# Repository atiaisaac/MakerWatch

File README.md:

# MakerWatch

## About
An open source smartwatch built by a maker for the maker community packed with interesting features and runs on the zephry RTOS

## Hardware
Outlined below is a breakdown of the hardware componenets considered for this design;

* __NINA-B306__ module (nrf52840 based microcontroller)
    * 1MB flash memory
    * 256KB of RAM
    * Bluetooth LE
    * internal pcb antenna
* __LSM6DSOX__ IMU with 6-DOF from stmicroelectronics. Primarily for step counting (pedometer) and other cool navigation gestures.
* __NPM1300__ single cell li-ion charger with power path managament. It also includes 2 buck converters capable of providing 200mA each and 3 LDOs. More than enough for our setup. When paired with the right nrf chipset, it can serve as a fuel guage as well.
* __MAX86141__ an AFE for optical data acquisition. Paired with MAX32664
* __MAX32664__ an ultra-low power biometric sensor hub with embedded firmware for heart rate monitoring and blood oxygen saturation measurement.
* __KX122__ paired with MAX32664 to compensate for artifacts of motion required for proper HRM and SpO2 measurement.
* __FIREFLY E2218__ true green color for health monitoring i.e HRM and pulse oximetry
* __SFH 7015__ hyper-red and infrared for HRM and pulse oximetry.
* __SFH 2703__ is a photodiode for capturing reflected light needed by the HRM and SpO2 algorithm
* 1.28'' round tft display with __GC9a01__ display driver
* __RV-8263-C8__ crystal to serve as real time clock/calendar
* __USB-C__ interface for easy flashing of firmware for developers/makers

The hardware setup is made up of two board stacked together back to back my a mezzinine connector. There is the main watch board and what I have dubbed the ppg board that has the leds for photoplethysemography.

## Software
The MakerWatch uses a usb-c as the main source of flashing new firmware. However, on the board, there are breakout pads that serve as Serial Wire Debug (SWD) interface for doing other cool stuff like ITM when paired with the right hardware programmer. In this version, wires will have to be soldered onto the pads before use.

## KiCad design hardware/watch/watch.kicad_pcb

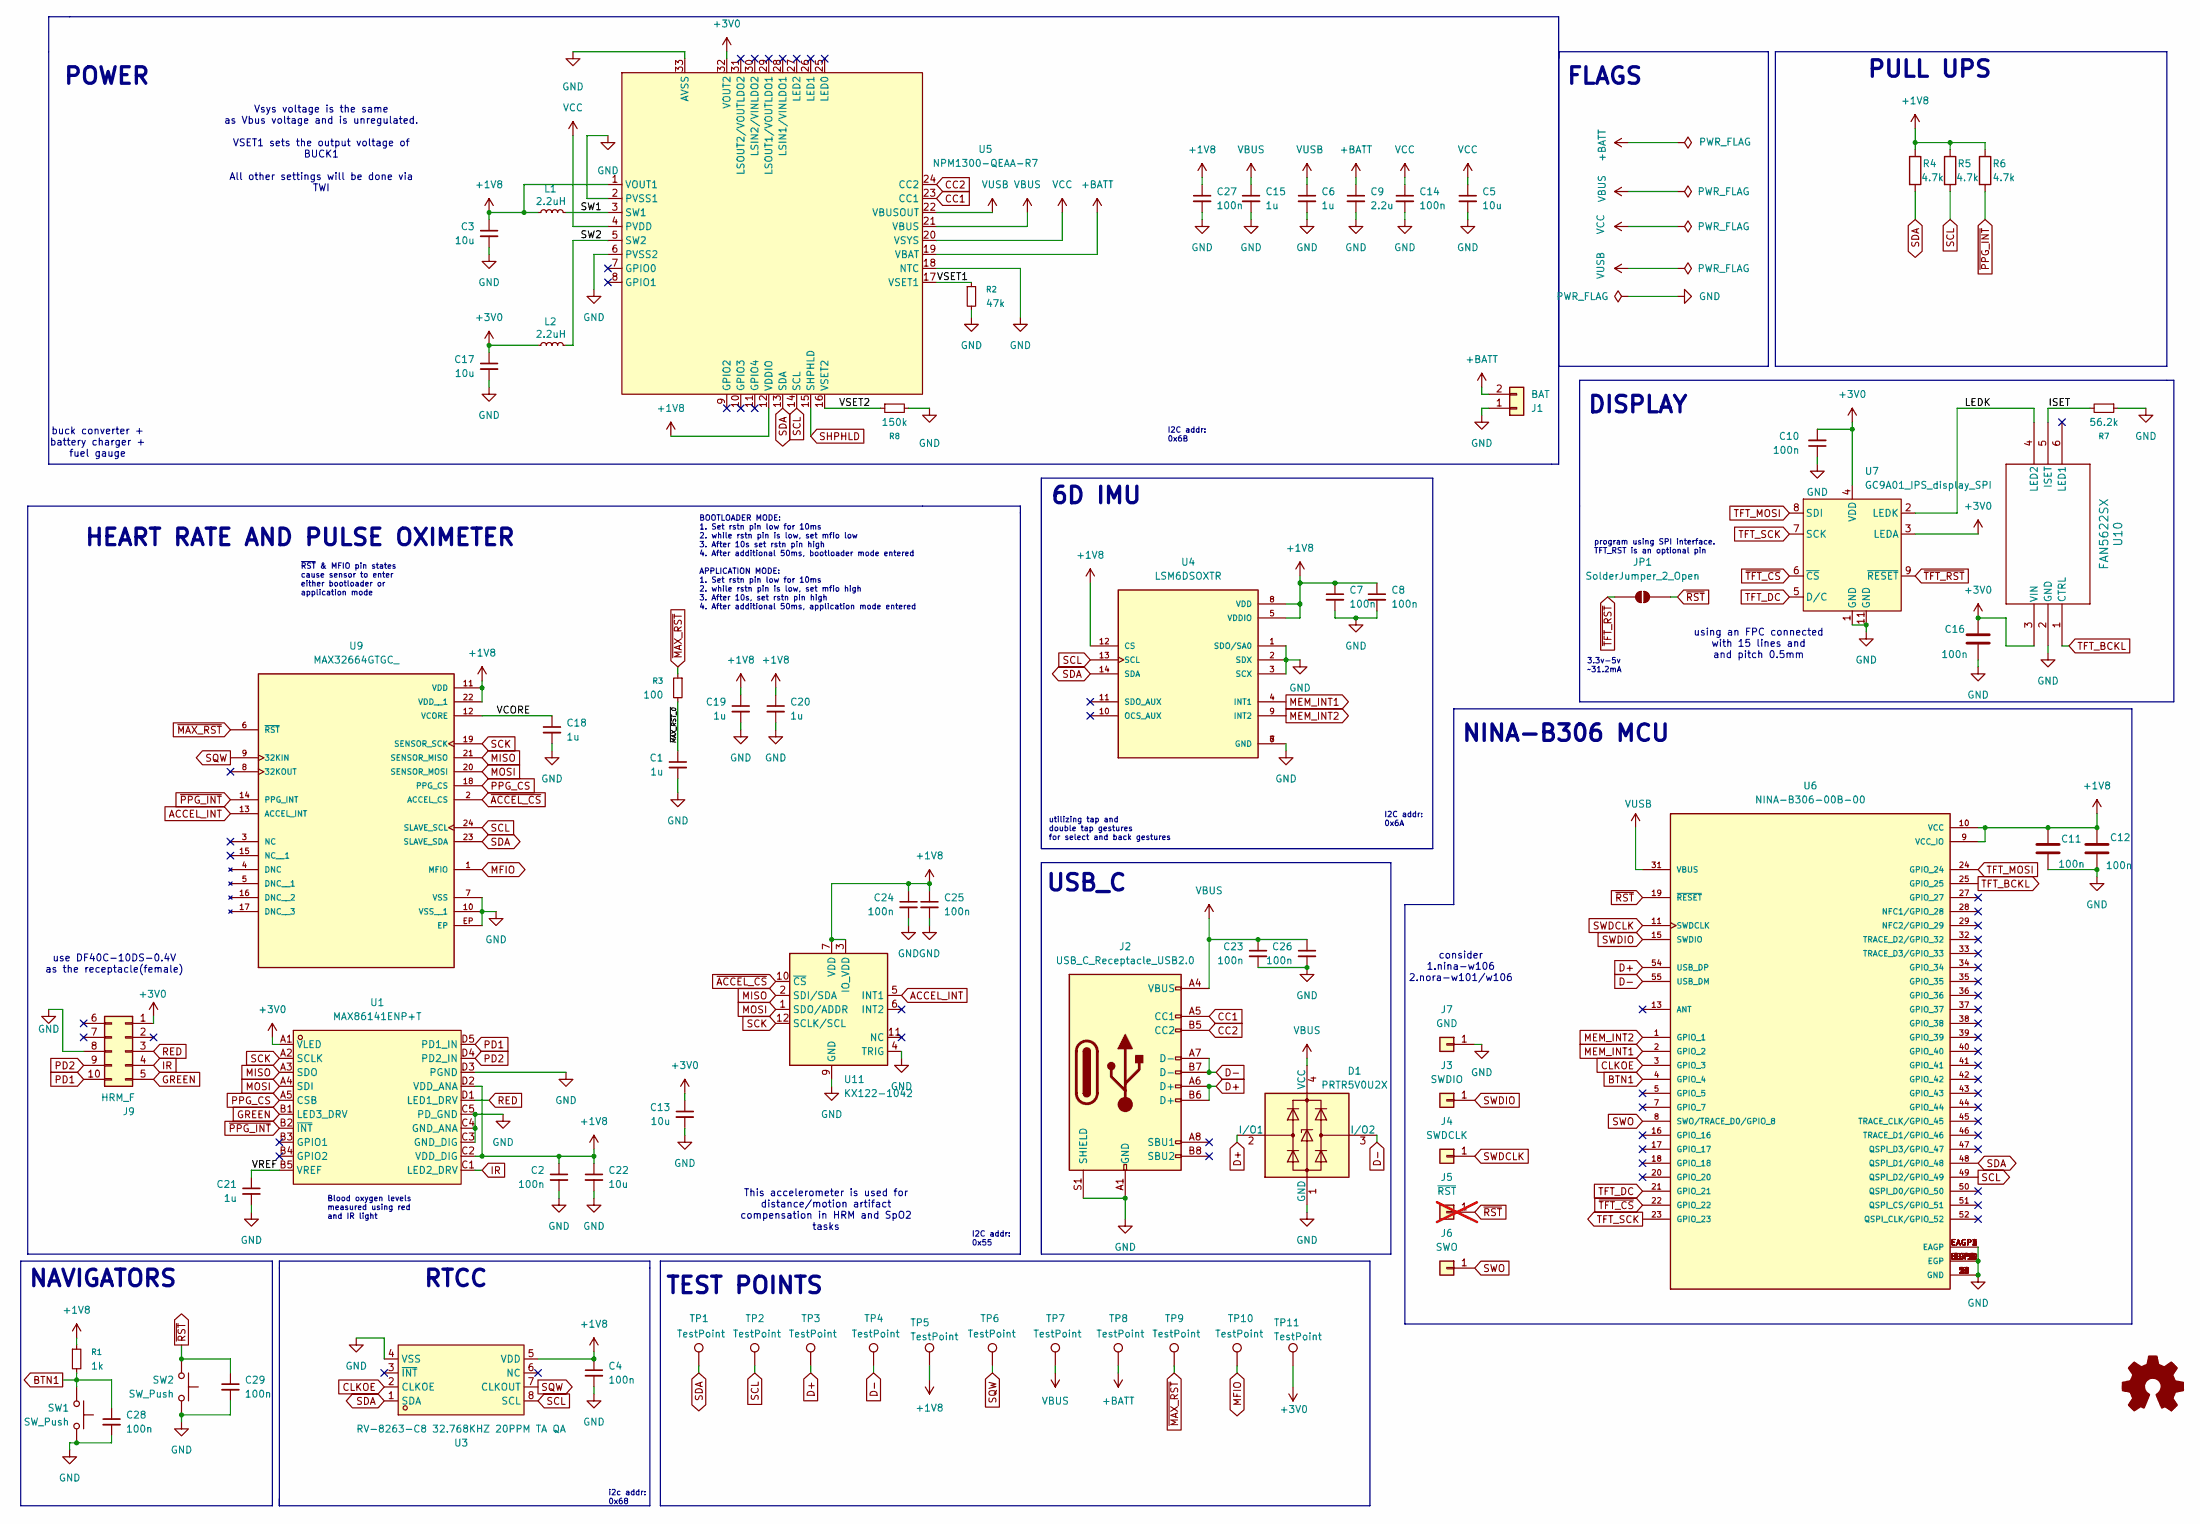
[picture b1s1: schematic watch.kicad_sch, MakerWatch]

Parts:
C1, C6, C15, C18, C19, C20, C21: 1u; C_0603_1608Metric
C2, C4, C7, C8, C10, C11, C12, C14, C16, C23, C24, C25, C26, C27, C28, C29: 100n; C_0603_1608Metric
C3, C5, C13, C17, C22: 10u; C_0603_1608Metric
C9: 2.2u; C_0603_1608Metric
D1: PRTR5V0U2X; SOT-143
J1: BAT; JST_ACH_BM02B-ACHSS-GAN-ETF_1x02-1MP_P1.20mm_Vertical
J2: USB_C_Receptacle_USB2.0; USB_C_Receptacle_GCT_USB4110; LCSC Part C3039307
J3: SWDIO; SolderWirePad_1x01_SMD_1x2mm
J4: SWDCLK; SolderWirePad_1x01_SMD_1x2mm
J5: ~{RST}; SolderWirePad_1x01_SMD_1x2mm; not fitted
J6: SWO; SolderWirePad_1x01_SMD_1x2mm
J7: GND; SolderWirePad_1x01_SMD_1x2mm
J9: HRM_F; Hirose_DF40B-10DS-0.4V_2x05-1MP_P0.4mm
JP1: SolderJumper_2_Open; SolderJumper-2_P1.3mm_Open_RoundedPad1.0x1.5mm
L1, L2: 2.2uH; L_0603_1608Metric
R1: 1k; R_0603_1608Metric
R2: 47k; R_0603_1608Metric
R3: 100; R_0603_1608Metric
R4, R5, R6: 4.7k; R_0603_1608Metric
R7: 56.2k; R_0603_1608Metric
R8: 150k; R_0603_1608Metric
SW1, SW2: SW_Push; SW_SPST_B3U-3000P-B; lcsc part C963349
TP1, TP2, TP3, TP4, TP5, TP6, TP7, TP8, TP9, TP10, TP11: TestPoint; TestPoint_Pad_D1.0mm
U1: MAX86141ENP+T; BGA-20_L2.0-W1.8-R4-C5-P0.40-TL; LCSC Part C5328762
U3: RV-8263-C8 32.768KHZ 20PPM TA QA; OSC-SMD_8P-L2.0-W1.2; LCSC Part C24955829
U4: LSM6DSOXTR; PQFN50P250X300X86-14N; PARTREV 3.0
U5: NPM1300-QEAA-R7; QFN-32_L5.0-W5.0-P0.50-TL-EP3.5; LCSC Part C7501206
U6: NINA-B306-00B-00; XCVR_NINA-B306-00B-00; PARTREV R07
U7: GC9A01_IPS_display_SPI; 15p_tft_P0.5; LCSC Part C262209
U9: MAX32664GTGC_; IC_MAX32664GTGC_; PARTREV 4
U10: FAN5622SX; SSOT6_3X1P7_ONS
U11: KX122-1042; LGA-12_2x2mm_P0.5mm

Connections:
+1V8: C2.1, C3.1, C4.1, C7.1, C8.1, C11.1, C12.1, C19.1, C20.1, C22.1, C24.1, C25.1, C27.1, L1.1, R1.1, R4.1, R5.1, R6.1, TP5.1 (1_1), U1.C2 (VDD_DIG), U1.D2 (VDD_ANA), U3.5 (VDD), U4.5 (VDDIO), U4.8 (VDD), U4.12 (CS), U5.1 (VOUT1), U5.12 (VDDIO), U6.9 (VCC_IO), U6.10 (VCC), U9.11 (VDD), U9.22 (VDD__1), U11.3 (IO_VDD), U11.7 (VDD)
+3V0: C10.2, C13.1, C16.1, C17.1, J9.1, L2.1, TP11.1 (1_1), U1.A1 (VLED), U5.32 (VOUT2), U7.3 (LEDA), U7.4 (VDD), U10.3 (VIN)
+BATT: C9.1, J1.2, TP8.1 (1_1), U5.19 (VBAT)
/ISET: R7.2, U10.5 (ISET)
/LEDK: U7.2 (LEDK), U10.4 (LED2)
/SW1: L1.2, U5.3 (SW1)
/SW2: L2.2, U5.5 (SW2)
/VCORE: C18.1, U9.12 (VCORE)
/VREF: C21.1, U1.B5 (VREF)
/VSET1: R2.1, U5.17 (VSET1)
/VSET2: R8.1, U5.16 (VSET2)
/~MAX_RST_0: C1.1, R3.2
ACCEL_INT: U9.13 (ACCEL_INT), U11.5 (INT1)
BTN1: C28.1, R1.2, SW1.2, U6.4 (GPIO_4)
CC1: J2.A5 (CC1), U5.23 (CC1)
CC2: J2.B5 (CC2), U5.24 (CC2)
CLKOE: U3.2 (CLKOE), U6.3 (GPIO_3)
D+: D1.2 (I/O1), J2.A6 (D+), J2.B6 (D+), TP3.1 (1_1), U6.54 (USB_DP)
D-: D1.3 (I/O2), J2.A7 (D-), J2.B7 (D-), TP4.1 (1_1), U6.55 (USB_DM)
GND: C1.2, C2.2, C3.2, C4.2, C5.2, C6.2, C7.2, C8.2, C9.2, C10.1, C11.2, C12.2, C13.2, C14.2, C15.2, C16.2, C17.2, C18.2, C19.2, C20.2, C21.2, C22.2, C23.2, C24.2, C25.2, C26.2, C27.2, C28.2, C29.2, D1.1 (GND), J1.1, J2.A1 (GND), J2.A12 (GND), J2.B1 (GND), J2.B12 (GND), J2.S1 (SHIELD), J7.1 (Pin_1_1), J9.8, R2.2, R7.1, R8.2, SW1.1, SW2.1, U1.C3 (GND_DIG), U1.C4 (GND_ANA), U1.C5 (PD_GND), U1.D3 (PGND), U3.4 (VSS), U4.1 (SDO/SA0), U4.2 (SDX), U4.3 (SCX), U4.6 (GND), U4.7 (GND), U5.2 (PVSS1), U5.6 (PVSS2), U5.18 (NTC), U5.33 (AVSS), U6.6 (GND), U6.12 (GND), U6.14 (GND), U6.26 (GND), U6.30 (GND), U6.53 (GND), U6.EAGP1 (EAGP), U6.EAGP2 (EAGP), U6.EAGP3 (EAGP), U6.EAGP4 (EAGP), U6.EGP1 (EGP), U6.EGP2 (EGP), U6.EGP3 (EGP), U6.EGP4 (EGP), U6.EGP5 (EGP), U6.EGP6 (EGP), U6.EGP7 (EGP), U6.EGP8 (EGP), U6.EGP9 (EGP), U6.EGP10 (EGP), U6.EGP11 (EGP), U6.EGP12 (EGP), U7.1 (GND), U7.11 (GND), U9.7 (VSS), U9.10 (VSS__1), U9.EP, U10.2 (GND), U11.4 (TRIG), U11.9 (GND)
GREEN: J9.5, U1.B1 (LED3_DRV)
IR: J9.4, U1.C1 (LED2_DRV)
MEM_INT1: U4.4 (INT1), U6.2 (GPIO_2)
MEM_INT2: U4.9 (INT2), U6.1 (GPIO_1)
MFIO: TP10.1 (1_1), U9.1 (MFIO)
MISO: U1.A3 (SDO), U9.21 (SENSOR_MISO), U11.2 (SDI/SDA)
MOSI: U1.A4 (SDI), U9.20 (SENSOR_MOSI), U11.1 (SDO/ADDR)
PD1: J9.10, U1.D5 (PD1_IN)
PD2: J9.9, U1.D4 (PD2_IN)
PPG_CS: U1.A5 (CSB), U9.18 (PPG_CS)
RED: J9.3, U1.D1 (LED1_DRV)
SCK: U1.A2 (SCLK), U9.19 (SENSOR_SCK), U11.12 (SCLK/SCL)
SCL: R5.2, TP2.1 (1_1), U3.8 (SCL), U4.13 (SCL), U5.14 (SCL), U6.49 (QSPI_D2/GPIO_49), U9.24 (SLAVE_SCL)
SDA: R4.2, TP1.1 (1_1), U3.1 (SDA), U4.14 (SDA), U5.13 (SDA), U6.48 (QSPI_D1/GPIO_48), U9.23 (SLAVE_SDA)
SHPHLD: U5.15 (SHPHLD)
SQW: TP6.1 (1_1), U3.7 (CLKOUT), U9.9 (32KIN)
SWDCLK: J4.1 (Pin_1_1), U6.11 (SWDCLK)
SWDIO: J3.1 (Pin_1_1), U6.15 (SWDIO)
SWO: J6.1 (Pin_1_1), U6.8 (SWO/TRACE_D0/GPIO_8)
TFT_BCKL: U6.25 (GPIO_25), U10.1 (CTRL)
TFT_DC: U6.21 (GPIO_21), U7.5 (D/C)
TFT_MOSI: U6.24 (GPIO_24), U7.8 (SDI)
TFT_SCK: U6.23 (GPIO_23), U7.7 (SCK)
VBUS: C15.1, C23.1, C26.1, D1.4 (VCC), J2.A4 (VBUS), J2.A9 (VBUS), J2.B4 (VBUS), J2.B9 (VBUS), TP7.1 (1_1), U5.21 (VBUS)
VCC: C5.1, C14.1, U5.4 (PVDD), U5.20 (VSYS)
VUSB: C6.1, U5.22 (VBUSOUT), U6.31 (VBUS)
~ACCEL_CS: U9.2 (ACCEL_CS), U11.10 (~CS)
~MAX_RST: R3.1, TP9.1 (1_1), U9.6 (~RST)
~PPG_INT: R6.2, U1.B2 (~INT), U9.14 (PPG_INT)
~RST: C29.1, J5.1, JP1.2 (B), SW2.2, U6.19 (~RESET)
~TFT_CS: U6.22 (GPIO_22), U7.6 (~CS)
~TFT_RST: JP1.1 (A), U7.9 (~RESET)

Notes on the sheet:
~{RST} & MFIO pin states cause sensor to enter either bootloader or application mode
Vsys voltage is the same as Vbus voltage and is unregulated. VSET1 sets the output voltage of BUCK1 All other settings will be done via TWI
NAVIGATORS
FLAGS
I2C addr: 0x6B
This accelerometer is used for distance/motion artifact compensation in HRM and SpO2 tasks
Blood oxygen levels measured using red and IR light
NINA-B306 MCU
using an FPC connected with 15 lines and and pitch 0.5mm
I2C addr: 0x55
POWER
use DF40C-10DS-0.4V as the receptacle(female)
i2c addr: 0x68
BOOTLOADER MODE: 1. Set rstn pin low for 10ms 2. while rstn pin is low, set mfio low 3. After 10s set rstn pin high 4. After additional 50ms, bootloader mode entered APPLICATION MODE: 1. Set rstn pin low for 10ms 2. while rstn pin is low, set mfio high 3. After 10s, set rstn pin high 4. After addit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
consider 1.nina-w106 2.nora-w101/w106
buck converter + battery charger + fuel gauge
USB_C
program using SPI interface. TFT_RST is an optional pin
PULL UPS
6D IMU
utilizing tap and double tap gestures for select and back gestures
3.3v-5v ~31.2mA
DISPLAY
TEST POINTS
HEART RATE AND PULSE OXIMETER
I2C addr: 0x6A
RTCC

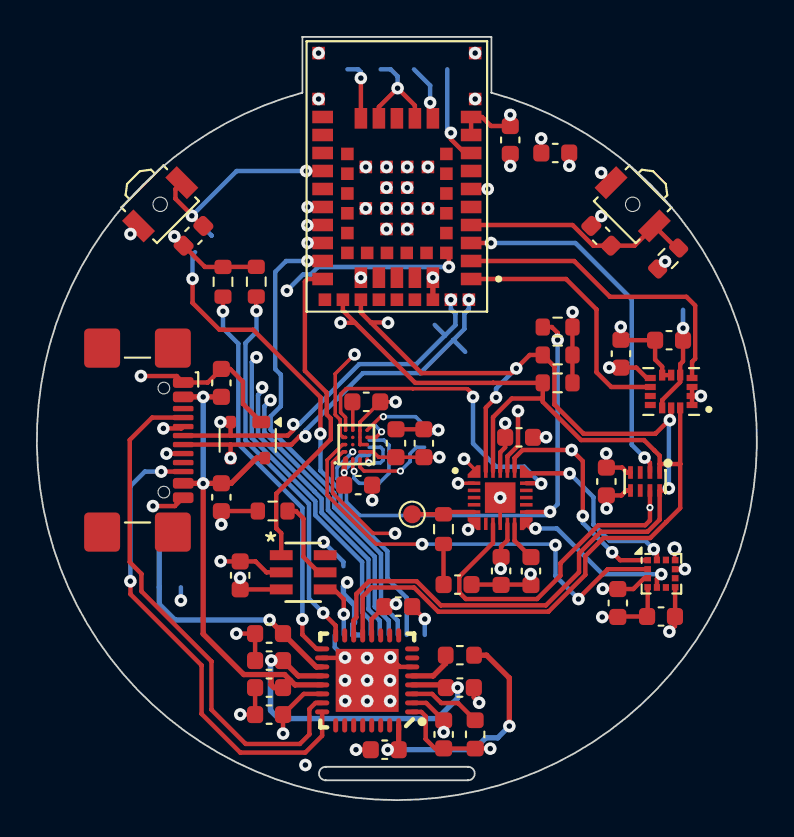
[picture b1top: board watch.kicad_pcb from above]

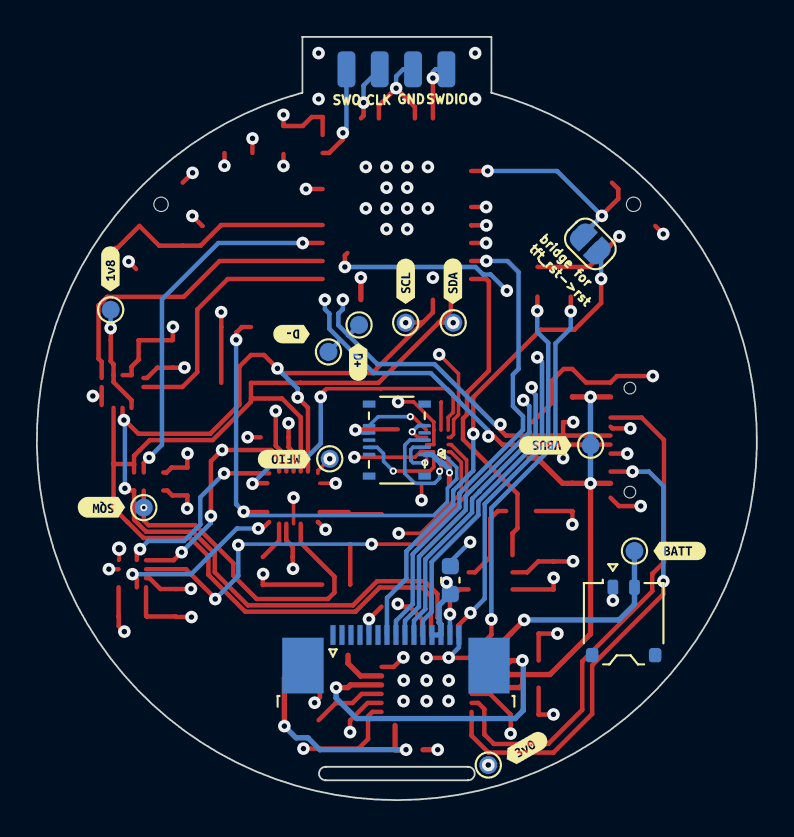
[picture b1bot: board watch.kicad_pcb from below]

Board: 4 copper layers, 40.0 x 42.4 mm, 80 parts (29 on the bottom side), 51 nets.

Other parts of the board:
kibuzzard-6A0A16D4: G***; kibuzzard-6A0A16D4
kibuzzard-6A0A1465: G***; kibuzzard-6A0A1465
kibuzzard-6A08DFE9: G***; kibuzzard-6A08DFE9
kibuzzard-6A08DFFD: G***; kibuzzard-6A08DFFD
kibuzzard-6A08E0DD: G***; kibuzzard-6A08E0DD
kibuzzard-6A08E0EE: G***; kibuzzard-6A08E0EE
kibuzzard-6A08E02E: G***; kibuzzard-6A08E02E
kibuzzard-6A08E019: G***; kibuzzard-6A08E019
kibuzzard-6A08E080: G***; kibuzzard-6A08E080
kibuzzard-6A08E121: G***; kibuzzard-6A08E121

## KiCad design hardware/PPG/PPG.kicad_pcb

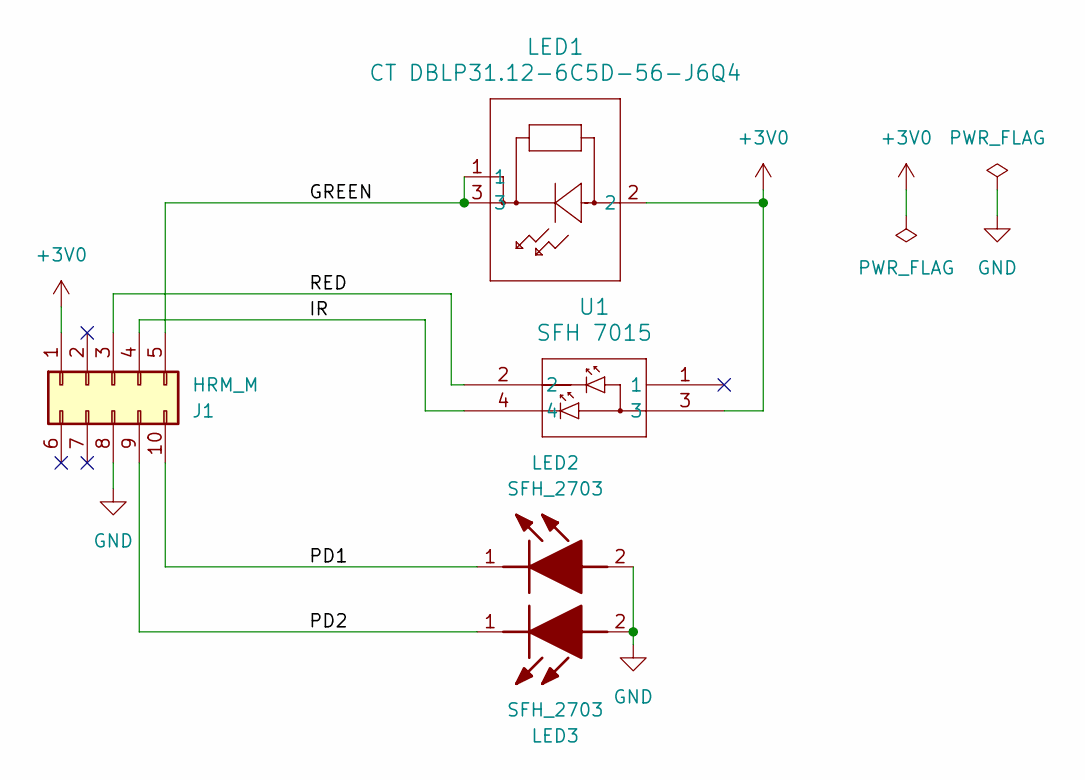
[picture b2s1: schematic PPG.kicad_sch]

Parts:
J1: HRM_M; Hirose_DF40C-10DP-0.4V_2x05-1MP_P0.4mm
LED1: CT DBLP31.12-6C5D-56-J6Q4; CT DBLP31.12-6C5D-56-J6Q4_OSR
LED2, LED3: SFH_2703; SFH2703; Mouser Part Number 720-SFH2703
U1: SFH 7015; SFH7015

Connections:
+3V0: J1.1, LED1.2, U1.3
/GREEN: J1.5, LED1.1, LED1.3
/IR: J1.4, U1.4
/PD1: J1.10, LED2.1 (K)
/PD2: J1.9, LED3.1 (K)
/RED: J1.3, U1.2
GND: J1.8, LED2.2 (A), LED3.2 (A)

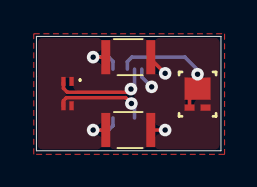
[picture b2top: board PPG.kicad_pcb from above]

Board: 2 copper layers, 10.2 x 6.3 mm, 5 parts (1 on the bottom side), 7 nets.

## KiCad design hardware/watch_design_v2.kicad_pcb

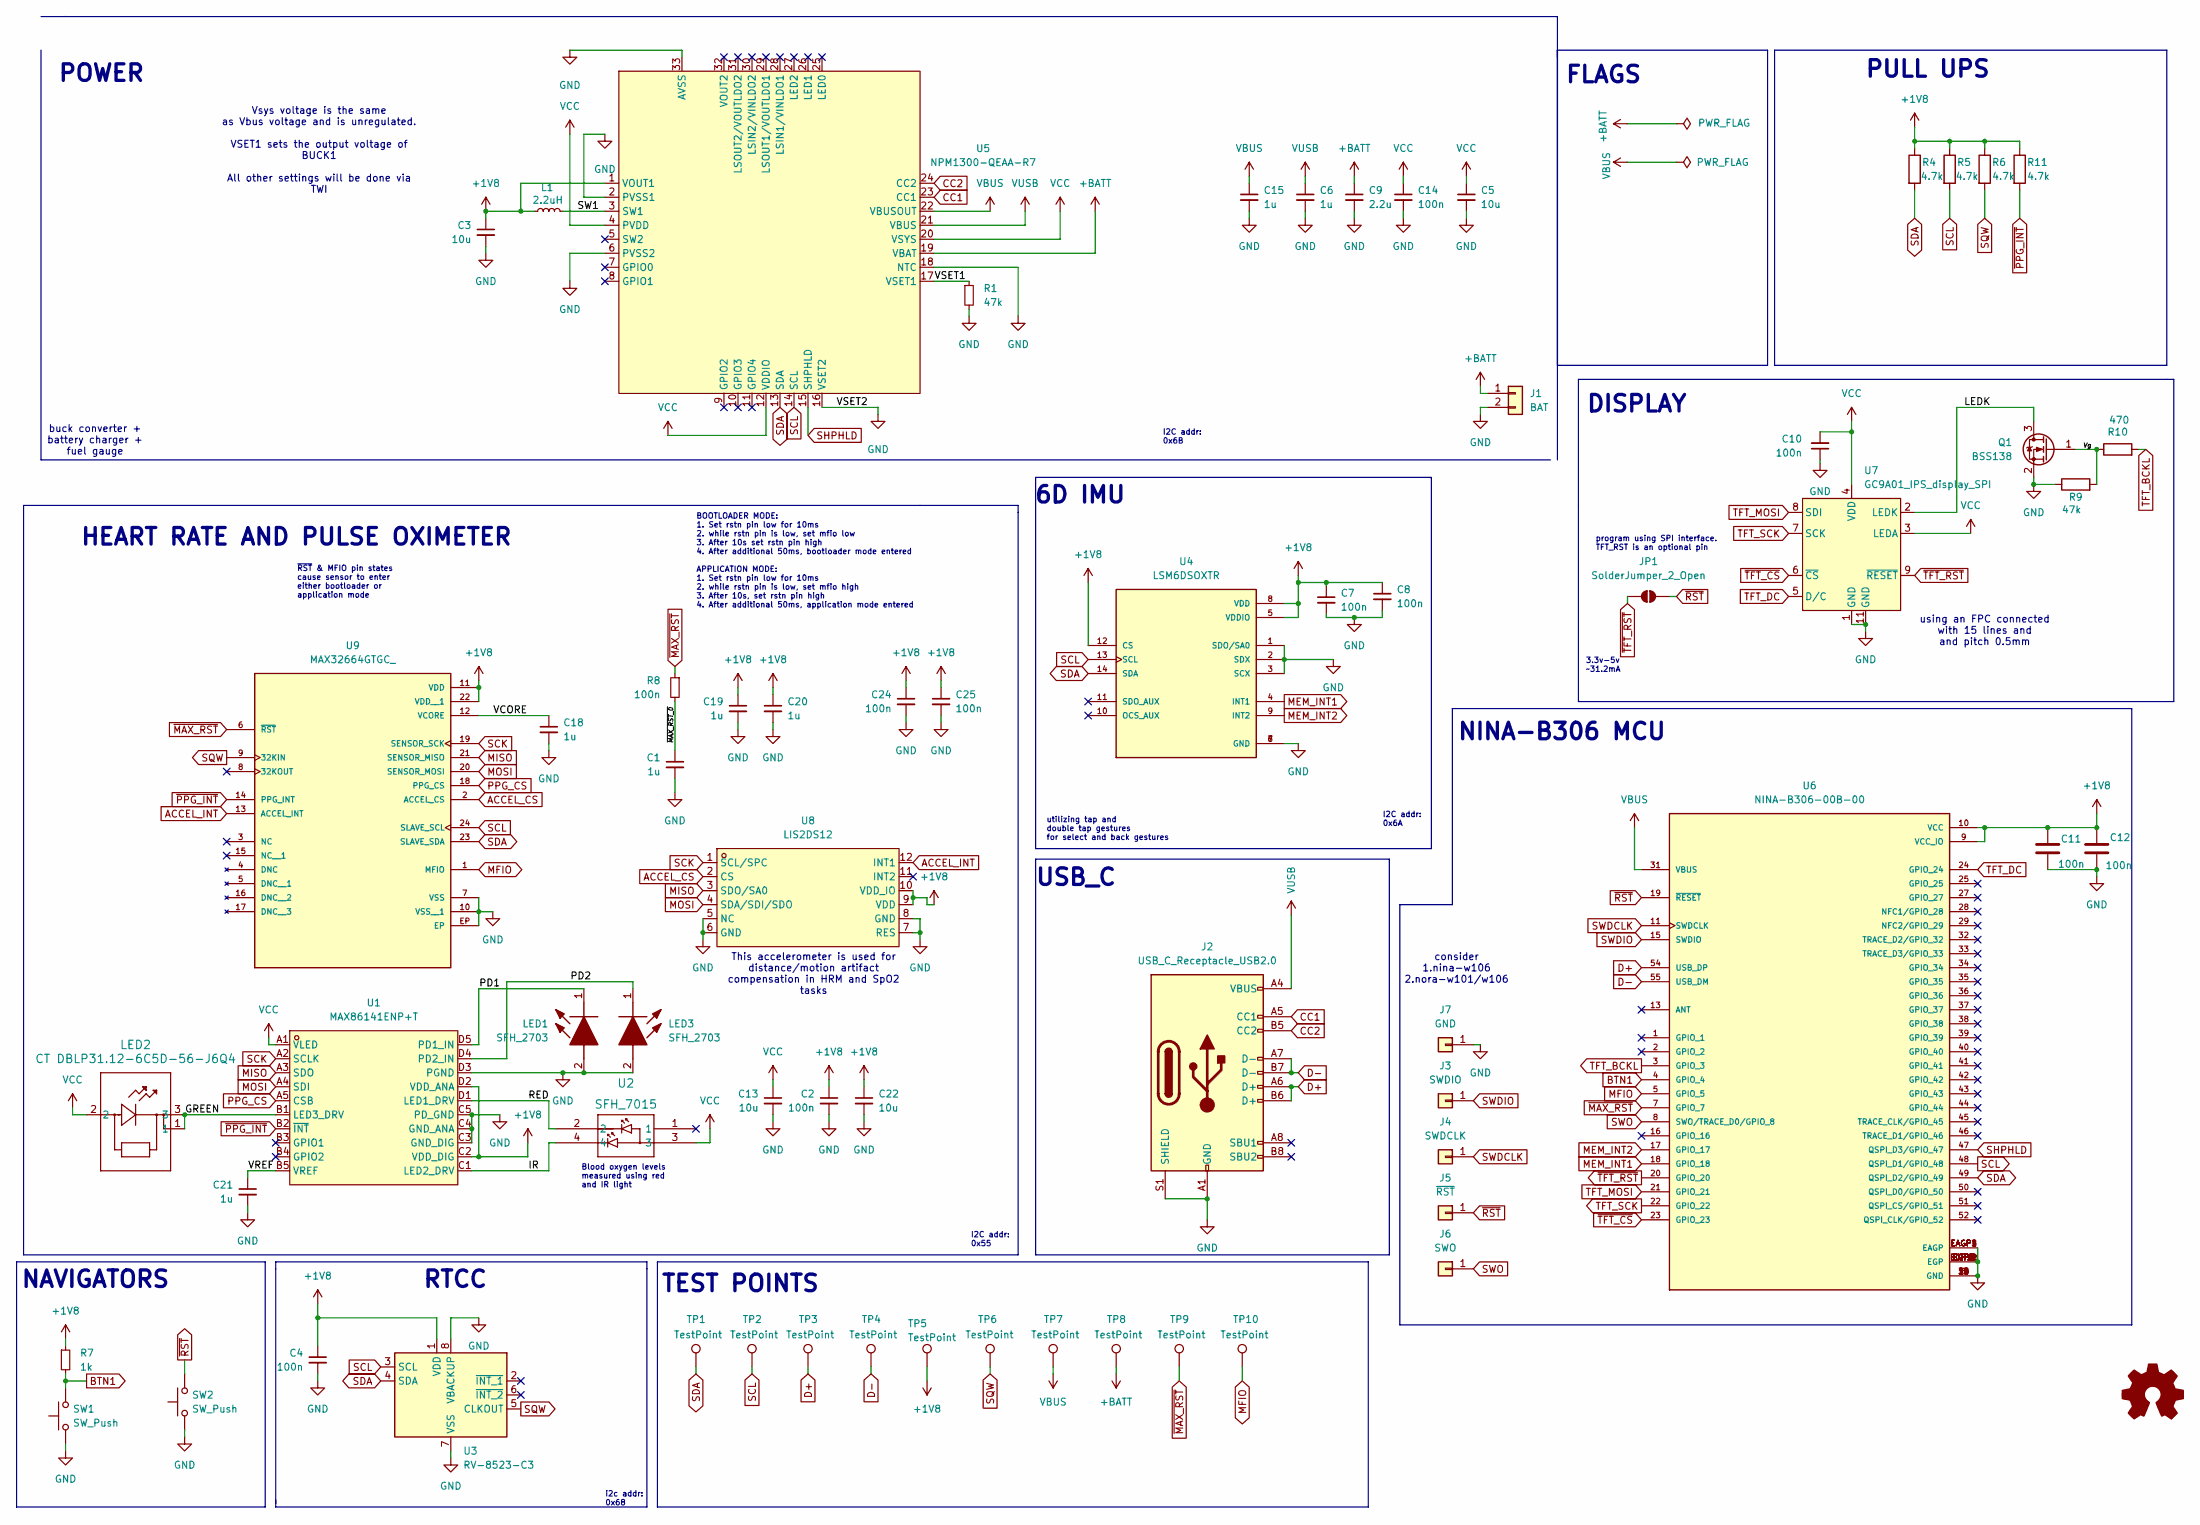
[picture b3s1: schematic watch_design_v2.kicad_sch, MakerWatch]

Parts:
C1, C6, C15, C18, C19, C20, C21: 1u; C_0603_1608Metric
C2, C4, C7, C8, C10, C11, C12, C14, C24, C25: 100n; C_0603_1608Metric
C3, C5, C13, C22: 10u; C_0603_1608Metric
C9: 2.2u; C_0603_1608Metric
J1: BAT; JST_ACH_BM02B-ACHSS-GAN-ETF_1x02-1MP_P1.20mm_Vertical
J2: USB_C_Receptacle_USB2.0; USB_C_Receptacle_GCT_USB4110; LCSC Part C3039307
J3: SWDIO; SolderWirePad_1x01_SMD_1x2mm
J4: SWDCLK; SolderWirePad_1x01_SMD_1x2mm
J5: ~{RST}; SolderWirePad_1x01_SMD_1x2mm
J6: SWO; SolderWirePad_1x01_SMD_1x2mm
J7: GND; SolderWirePad_1x01_SMD_1x2mm
JP1: SolderJumper_2_Open; SolderJumper-2_P1.3mm_Open_RoundedPad1.0x1.5mm
L1: 2.2uH; L_0603_1608Metric
LED1, LED3: SFH_2703; SFH2703; Mouser Part Number 720-SFH2703
LED2: CT DBLP31.12-6C5D-56-J6Q4; CT DBLP31.12-6C5D-56-J6Q4_OSR
Q1: BSS138; SOT-23
R1, R9: 47k; R_0603_1608Metric
R4, R5, R6, R11: 4.7k; R_0603_1608Metric
R7: 1k; R_0603_1608Metric
R8: 100n; R_0603_1608Metric
R10: 470; R_0603_1608Metric
SW1, SW2: SW_Push; SW-SMD_LXTD-0204-034
TP1, TP2, TP3, TP4, TP5, TP6, TP7, TP8, TP9, TP10: TestPoint; TestPoint_Pad_D1.0mm
U1: MAX86141ENP+T; BGA-20_L2.0-W1.8-R4-C5-P0.40-TL; LCSC Part C5328762
U2: SFH_7015; SFH 7015_OSR
U3: RV-8523-C3; RTC_SMD_MicroCrystal_C3_2.5x3.7mm; LCSC Part C5366557
U4: LSM6DSOXTR; PQFN50P250X300X86-14N; PARTREV 3.0; LCSC Part C481766
U5: NPM1300-QEAA-R7; QFN-32_L5.0-W5.0-P0.50-TL-EP3.5; LCSC Part C7501206
U6: NINA-B306-00B-00; XCVR_NINA-B306-00B-00; PARTREV R07; LCSC Part C6127317
U7: GC9A01_IPS_display_SPI; 15p_tft_P0.5; LCSC Part C262209
U8: LIS2DS12; LGA-12_L2.0-W2.0-P0.50-BL; LCSC Part C5337244
U9: MAX32664GTGC_; IC_MAX32664GTGC_; PARTREV 4; LCSC Part C5344734

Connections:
+1V8: C2.1, C3.1, C4.1, C7.1, C8.1, C11.1, C12.1, C19.1, C20.1, C22.1, C24.1, C25.1, L1.1, R4.1, R5.1, R6.1, R7.1, R11.1, TP5.1, U1.C2 (VDD_DIG), U1.D2 (VDD_ANA), U3.1 (VDD), U4.5 (VDDIO), U4.8 (VDD), U4.12 (CS), U5.1 (VOUT1), U6.9 (VCC_IO), U6.10 (VCC), U8.9 (VDD), U8.10 (VDD_IO), U9.11 (VDD), U9.22 (VDD__1)
+BATT: C9.1, J1.1, TP8.1, U5.19 (VBAT)
/GREEN: LED2.1, LED2.3, U1.B1 (LED3_DRV)
/IR: U1.C1 (LED2_DRV), U2.4
/LEDK: Q1.3 (D), U7.2 (LEDK)
/PD1: LED1.1 (K), U1.D5 (PD1_IN)
/PD2: LED3.1 (K), U1.D4 (PD2_IN)
/RED: U1.D1 (LED1_DRV), U2.2
/SW1: L1.2, U5.3 (SW1)
/VCORE: C18.1, U9.12 (VCORE)
/VREF: C21.1, U1.B5 (VREF)
/VSET1: R1.1, U5.17 (VSET1)
/Vg: Q1.1 (G), R9.2, R10.1
/~MAX_RST_0: C1.1, R8.2
ACCEL_CS: U8.2 (CS), U9.2 (ACCEL_CS)
ACCEL_INT: U8.12 (INT1), U9.13 (ACCEL_INT)
BTN1: R7.2, SW1.2, U6.4 (GPIO_4)
CC1: J2.A5 (CC1), U5.23 (CC1)
CC2: J2.B5 (CC2), U5.24 (CC2)
D+: J2.A6 (D+), J2.B6 (D+), TP3.1, U6.54 (USB_DP)
D-: J2.A7 (D-), J2.B7 (D-), TP4.1, U6.55 (USB_DM)
GND: C1.2, C2.2, C3.2, C4.2, C5.2, C6.2, C7.2, C8.2, C9.2, C10.1, C11.2, C12.2, C13.2, C14.2, C15.2, C18.2, C19.2, C20.2, C21.2, C22.2, C24.2, C25.2, J1.2, J2.A1 (GND), J2.A12 (GND), J2.B1 (GND), J2.B12 (GND), J2.S1 (SHIELD), J7.1, LED1.2 (A), LED3.2 (A), Q1.2 (S), R1.2, R9.1, SW1.1, SW2.1, U1.C3 (GND_DIG), U1.C4 (GND_ANA), U1.C5 (PD_GND), U1.D3 (PGND), U3.7 (VSS), U3.8 (VBACKUP), U4.1 (SDO/SA0), U4.2 (SDX), U4.3 (SCX), U4.6 (GND), U4.7 (GND), U5.2 (PVSS1), U5.6 (PVSS2), U5.16 (VSET2), U5.18 (NTC), U5.33 (AVSS), U6.6 (GND), U6.12 (GND), U6.14 (GND), U6.26 (GND), U6.30 (GND), U6.53 (GND), U6.EAGP1 (EAGP), U6.EAGP2 (EAGP), U6.EAGP3 (EAGP), U6.EAGP4 (EAGP), U6.EGP1 (EGP), U6.EGP2 (EGP), U6.EGP3 (EGP), U6.EGP4 (EGP), U6.EGP5 (EGP), U6.EGP6 (EGP), U6.EGP7 (EGP), U6.EGP8 (EGP), U6.EGP9 (EGP), U6.EGP10 (EGP), U6.EGP11 (EGP), U6.EGP12 (EGP), U7.1 (GND), U7.11 (GND), U8.5 (NC), U8.6 (GND), U8.7 (RES), U8.8 (GND), U9.7 (VSS), U9.10 (VSS__1), U9.EP
MEM_INT1: U4.4 (INT1), U6.18 (GPIO_18)
MEM_INT2: U4.9 (INT2), U6.17 (GPIO_17)
MFIO: TP10.1, U6.5 (GPIO_5), U9.1 (MFIO)
MISO: U1.A3 (SDO), U8.3 (SDO/SA0), U9.21 (SENSOR_MISO)
MOSI: U1.A4 (SDI), U8.4 (SDA/SDI/SDO), U9.20 (SENSOR_MOSI)
PPG_CS: U1.A5 (CSB), U9.18 (PPG_CS)
SCK: U1.A2 (SCLK), U8.1 (SCL/SPC), U9.19 (SENSOR_SCK)
SCL: R5.2, TP2.1, U3.3 (SCL), U4.13 (SCL), U5.14 (SCL), U6.48 (QSPI_D1/GPIO_48), U9.24 (SLAVE_SCL)
SDA: R4.2, TP1.1, U3.4 (SDA), U4.14 (SDA), U5.13 (SDA), U6.49 (QSPI_D2/GPIO_49), U9.23 (SLAVE_SDA)
SHPHLD: U5.15 (SHPHLD), U6.47 (QSPI_D3/GPIO_47)
SQW: R6.2, TP6.1, U3.5 (CLKOUT), U9.9 (32KIN)
SWDCLK: J4.1, U6.11 (SWDCLK)
SWDIO: J3.1, U6.15 (SWDIO)
SWO: J6.1, U6.8 (SWO/TRACE_D0/GPIO_8)
TFT_BCKL: R10.2, U6.3 (GPIO_3)
TFT_DC: U6.24 (GPIO_24), U7.5 (D/C)
TFT_MOSI: U6.21 (GPIO_21), U7.8 (SDI)
TFT_SCK: U6.22 (GPIO_22), U7.7 (SCK)
VBUS: C15.1, TP7.1, U5.22 (VBUSOUT), U6.31 (VBUS)
VCC: C5.1, C10.2, C13.1, C14.1, LED2.2, U1.A1 (VLED), U2.3, U5.4 (PVDD), U5.12 (VDDIO), U5.20 (VSYS), U7.3 (LEDA), U7.4 (VDD)
VUSB: C6.1, J2.A4 (VBUS), J2.A9 (VBUS), J2.B4 (VBUS), J2.B9 (VBUS), U5.21 (VBUS)
~MAX_RST: R8.1, TP9.1, U6.7 (GPIO_7), U9.6 (~RST)
~PPG_INT: R11.2, U1.B2 (~INT), U9.14 (PPG_INT)
~RST: J5.1, JP1.2 (B), SW2.2, U6.19 (~RESET)
~TFT_CS: U6.23 (GPIO_23), U7.6 (~CS)
~TFT_RST: JP1.1 (A), U6.20 (GPIO_20), U7.9 (~RESET)

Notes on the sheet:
3.3v-5v ~31.2mA
NAVIGATORS
RTCC
~{RST} & MFIO pin states cause sensor to enter either bootloader or application mode
utilizing tap and double tap gestures for select and back gestures
DISPLAY
This accelerometer is used for distance/motion artifact compensation in HRM and SpO2 tasks
using an FPC connected with 15 lines and and pitch 0.5mm
i2c addr: 0x68
program using SPI interface. TFT_RST is an optional pin
consider 1.nina-w106 2.nora-w101/w106
I2C addr: 0x6A
USB_C
Blood oxygen levels measured using red and IR light
HEART RATE AND PULSE OXIMETER
buck converter + battery charger + fuel gauge
POWER
6D IMU
FLAGS
BOOTLOADER MODE: 1. Set rstn pin low for 10ms 2. while rstn pin is low, set mfio low 3. After 10s set rstn pin high 4. After additional 50ms, bootloader mode entered APPLICATION MODE: 1. Set rstn pin low for 10ms 2. while rstn pin is low, set mfio high 3. After 10s, set rstn pin high 4. After addit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
TEST POINTS
PULL UPS
Vsys voltage is the same as Vbus voltage and is unregulated. VSET1 sets the output voltage of BUCK1 All other settings will be done via TWI
I2C addr: 0x55
NINA-B306 MCU
I2C addr: 0x6B

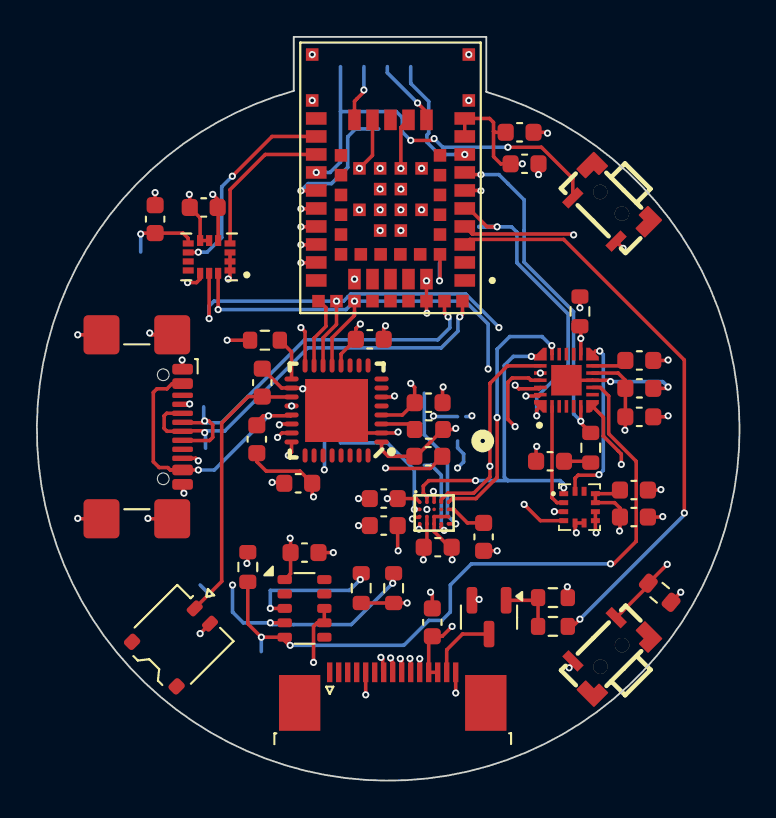
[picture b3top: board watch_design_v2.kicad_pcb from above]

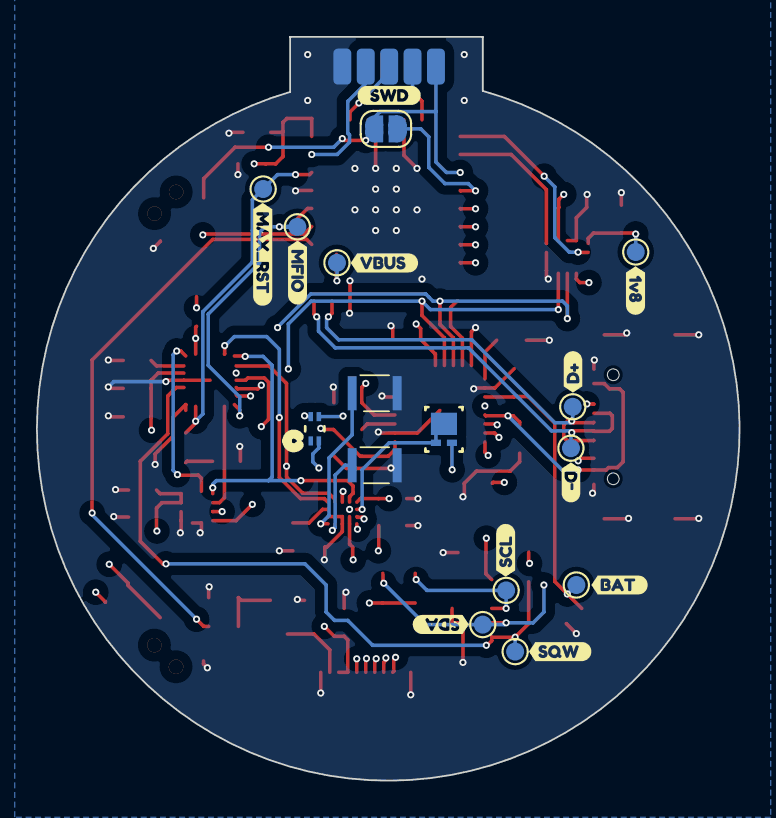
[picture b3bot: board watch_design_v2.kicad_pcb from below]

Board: 4 copper layers, 39.0 x 41.3 mm, 76 parts (31 on the bottom side), 48 nets.

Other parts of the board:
kibuzzard-685D65B1: G***; kibuzzard-685D65B1
kibuzzard-685D654C: G***; kibuzzard-685D654C
kibuzzard-685D657A: G***; kibuzzard-685D657A
kibuzzard-685D6522: G***; kibuzzard-685D6522
kibuzzard-685D6535: G***; kibuzzard-685D6535
kibuzzard-685D6567: G***; kibuzzard-685D6567
kibuzzard-685D6588: G***; kibuzzard-685D6588
kibuzzard-6862C5FF: G***; kibuzzard-6862C5FF
kibuzzard-6862C63C: G***; kibuzzard-6862C63C
kibuzzard-686159F7: G***; kibuzzard-686159F7
kibuzzard-68615877: G***; kibuzzard-68615877
